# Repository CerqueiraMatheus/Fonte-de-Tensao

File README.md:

# Fonte de Tensão

Projeto de uma fonte de tensão realizada para a disciplina de [Eletrônica para Computação](https://uspdigital.usp.br/jupiterweb/obterDisciplina?sgldis=SSC0180&codcur=55041&codhab=0) do curso de Ciências de Computação do ICMC-USP, ministrada por Eduardo Valle Simões.

## Especificações

> Construir uma fonte de tensão regulada, ajustável, com onda completa, que receba 127V a 220V e tenha como saída de 3V até 12V, fornecendo 100mA a 12V.

## Introdução aos componentes

*Clique no nome do elemento para mais informações.*

Nome                 | Funcionalidade básica
:--------------------|:--------------------------
[Fonte de alimentação](https://pt.wikipedia.org/wiki/Fonte_de_alimenta%C3%A7%C3%A3o) | Prover energia ao circuito
[Transformador](https://pt.wikipedia.org/wiki/Transformador) | Tratar a energia para o circuito
[Diodo](https://pt.wikipedia.org/wiki/Diodo_semicondutor) | Fazer com que a corrente flua num sentido só
[Ponte de diodos](https://pt.wikipedia.org/wiki/Retificador_de_onda_completa#Retificador_em_ponte) | Tratar o direcionamento da energia
[Capacitor](https://pt.wikipedia.org/wiki/Capacitor) | Armazenar quantidades de energia
[Resistor](https://pt.wikipedia.org/wiki/Resistor) | Limitar a corrente num circuito
[Diodo Zener](https://pt.wikipedia.org/wiki/Diodo_Zener) | Regula a tensão
[Potenciômetro](https://pt.wikipedia.org/wiki/Potenci%C3%B4metro) | "Divide" a tensão num circuito
[Transistor](https://pt.wikipedia.org/wiki/Trans%C3%ADstor) | "Amplificar" / barrar a corrente

## Produções

1. Aplicamos cálculos referentes à Fonte de Tensão de Onda Completa (sem regulação) com base no livro base da disciplina. Para facilitar, fizemos um compilado num [código em C](calculator.c). Dele, partindo de uma saída esperada de 25V (referente ao transformador) e 0,11A (suficiente para o circuito), combinadas a um ripple de 2,5V extraímos:

* A relação do transformador (0,1534);
* As tensões de pico (179V no primário e 27V no secundário);
* O capacitor ideal (> 314µF).
  
2. Construímos o projeto na ferramenta online Falstad: [teste o circuito no Falstad clicando aqui](http://tinyurl.com/ybr8kftz).

3. Elaboramos uma lista de componentes no Baú da Eletrônica (e adaptamos o projeto no Falstad).

4. O circuito completo está explicado em vídeo: [acesse-o no YouTube clicando aqui](https://youtu.be/ek0Hfe_L8pc).

5. Elaboramos o projeto no Eagle (PCB e Esquemático) para impressão da placa. Os arquivos estão nomeados com "fonte-de-tensao" na raiz desta página.

## Circuito no Falstad

Como base para o projeto, construímos o seguinte circuito:

<div align="center">

</div>

[Acesse o link do Falstad para poder ver e editar a simulação](http://tinyurl.com/ybr8kftz).

## Componentes do circuito

*Clique no nome do elemento para acessá-lo na loja escolhida (Baú da Eletrônica).*

Nome | Especificação básica | Justificativa | Valor
:----:|:-------------------:|:-------------:|:------:
[Transformador](https://www.baudaeletronica.com.br/transformador-trafo-12v-12v-500ma-110-220vac.html) | Entrada: 127V/220V / Saída: 12V+12V 500mA | Custo baixo e reusabilidade | R$22,23
[Ponte de Diodos](https://www.baudaeletronica.com.br/ponte-retificadora-kbpc1010.html) ¹ | 10A / 1000V | Suficiente para a corrente na ponte (aproximadamente 1,3A) | R$3,79 
[Capacitor](https://www.baudaeletronica.com.br/capacitor-eletrolitico-330uf-100v.html) ¹ | 330µF / 100V | Suficiente para suportar a entrada (~27V e 1,3A) e prover energia regulada para o circuito | R$3,32
[Resistor (1)](https://www.baudaeletronica.com.br/resistor-5k6-5-1-4w.html) | 5.6kΩ | Mantém a corrente sobre o Zener menor que 1mA e maior que 0,25mA (corrente mínima, Izk) | R$0,08
[Diodo Zener](https://www.baudaeletronica.com.br/diodo-zener-1n4743-13v-1w.html) | 13V / 1W | "Corta" a tensão a 13V | R$0,20
[Potenciômetro](https://www.baudaeletronica.com.br/potenciometro-linear-de-10k-10000.html) | 10kΩ | Mantém a tensão entre 0V e 12V | R$1,46
[Resistor (2)](https://www.baudaeletronica.com.br/resistor-5k6-5-1-4w.html) | 5.6kΩ | Adapta o potenciômetro e mantém a tensão de 3V a 12V | R$0,08
[Transistor](https://www.baudaeletronica.com.br/transistor-npn-2n3904.html) ¹ | Corrente máxima no coletor de 200mA e tensão máxima do coletor 40V | Suporta os 25V no coletor e tem mínimo de 0,25mA na base | R$0,17

*¹ Os componentes marcados têm características superiores às necessárias, mas por razões de disponibilidade na loja escolhida, foram selecionados.*

## Esquemático do circuito no Eagle

O primeiro passo para a construção no Eagle se deu pela construção do Esquemático, com exceção do transformador, por indisponibilidade, e foi substituído por conexões de entrada e saída. Quanto às peças utilizadas, selecionamos as mais próximas às listadas para compra no projeto, sendo a Ponte de Diodos e o Transistor NPN representações exatas, o Diodo Zener tendo dimensões idênticas ao selecionado e os demais componentes com o mesmo formato e dimensões muito próximas. Os arquivos estão nomeados utilizados como "fonte-de-tensao" na raiz desta página.

A representação da Ponte de Diodos KBPC1010 é customizada, de autoria de SamacSys.

<div align="center">

</div>

## PCB do circuito no Eagle

A partir do Esquemático, por fim, construímos o PCB para a impressão do circuito.

<div align="center">

</div>

## Informações úteis

Caso queira construir este projeto, recomendamos, além dos links já disponibilizados, que

1. [Acesse a página da disciplina no GitLab](https://gitlab.com/simoesusp/disciplinas/-/tree/master/SSC0180-Eletronica-para-Computacao);

2. [Leia o livro base da disciplina](https://www.amazon.com.br/Eletr%C3%B4nica-B%C3%A1sica-Computa%C3%A7%C3%A3o-Annibal-Junior/dp/8521616996).

## Autoria

[Matheus Henrique de C. Pinto](https://github.com/cerqueiramatheus) n° USP: 11911104.

[Pedro Lucas M. de Castro](https://github.com/pedrolmcastro) n° USP: 11795784.

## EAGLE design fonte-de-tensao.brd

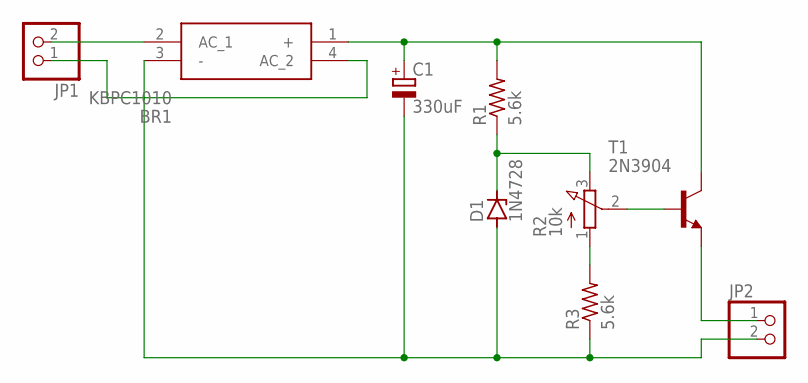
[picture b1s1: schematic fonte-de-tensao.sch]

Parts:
BR1: KBPC1010
C1: 330uF; E3,5-10
D1: 1N4728; DO41Z10
JP1, JP2: PINHD-1X2; 1X02
R1, R3: 5.6k; 0309/12
R2: 10k; 3RP/1610N
T1: 2N3904; TO92

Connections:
unnamed: BR1.4 (AC_2), JP1.1
unnamed: BR1.2 (AC_1), JP1.2
unnamed: BR1.1 (+), C1.+, R1.2, T1.1 (C)
unnamed: D1.C, R1.1, R2.3 (E)
unnamed: R2.1 (A), R3.2
unnamed: BR1.3 (-), C1.-, D1.A, JP2.2, R3.1
unnamed: R2.2 (S), T1.2 (B)
unnamed: JP2.1, T1.3 (E)

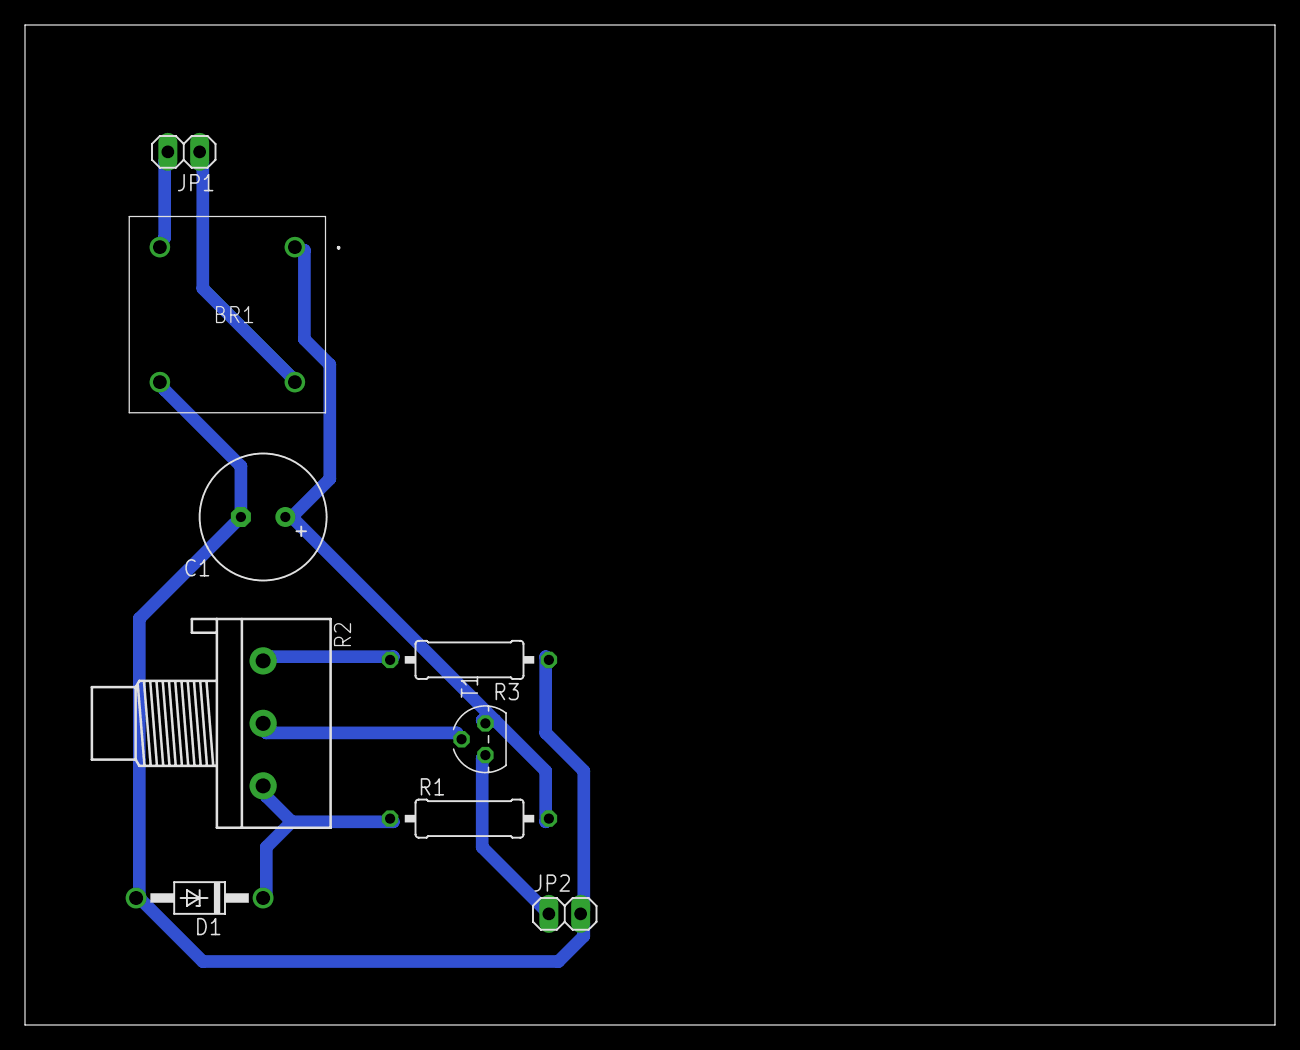
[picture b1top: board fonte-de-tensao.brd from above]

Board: 2 copper layers, 100.0 x 80.0 mm, 9 parts (0 on the bottom side), 8 nets.

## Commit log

2020-06-02 Criação do README
2020-06-07 Adding no regulated calculator
2020-06-13 README update
2020-06-13 Adding table
2020-06-13 Left alignment
2020-06-13 Adding circuit components
2020-06-13 Testing
2020-06-13 Adding components
2020-06-13 Adding values
2020-06-13 Updating values
2020-06-13 Updating prics
2020-06-14 Potenciometer update
2020-06-14 Update infos
2020-06-14 Adding image
2020-06-14 Fixing image
2020-06-14 Updating Falstad link
2020-06-14 FIxing Falstad link
2020-06-16 Adding prices
2020-06-16 Adding transistor values
2020-06-16 Adding nUSP
2020-06-16 Fixing nUSP
2020-06-16 Fixing transistor
2020-06-16 Adding video
2020-06-16 Fixing links
2020-06-16 FIxing values
2020-06-16 Fixing ¹
2020-06-16 Fixing Produções
2020-06-16 General fixes
2020-06-29 Fixing calculator
2020-06-30 Adding pico
2020-06-30 Fixing README
2020-06-30 Fixing diodes
2020-06-30 Fixing PCB
2020-06-30 Adding infos
2020-06-30 Fixing infos
2020-06-30 Adding YouTube link on readme
